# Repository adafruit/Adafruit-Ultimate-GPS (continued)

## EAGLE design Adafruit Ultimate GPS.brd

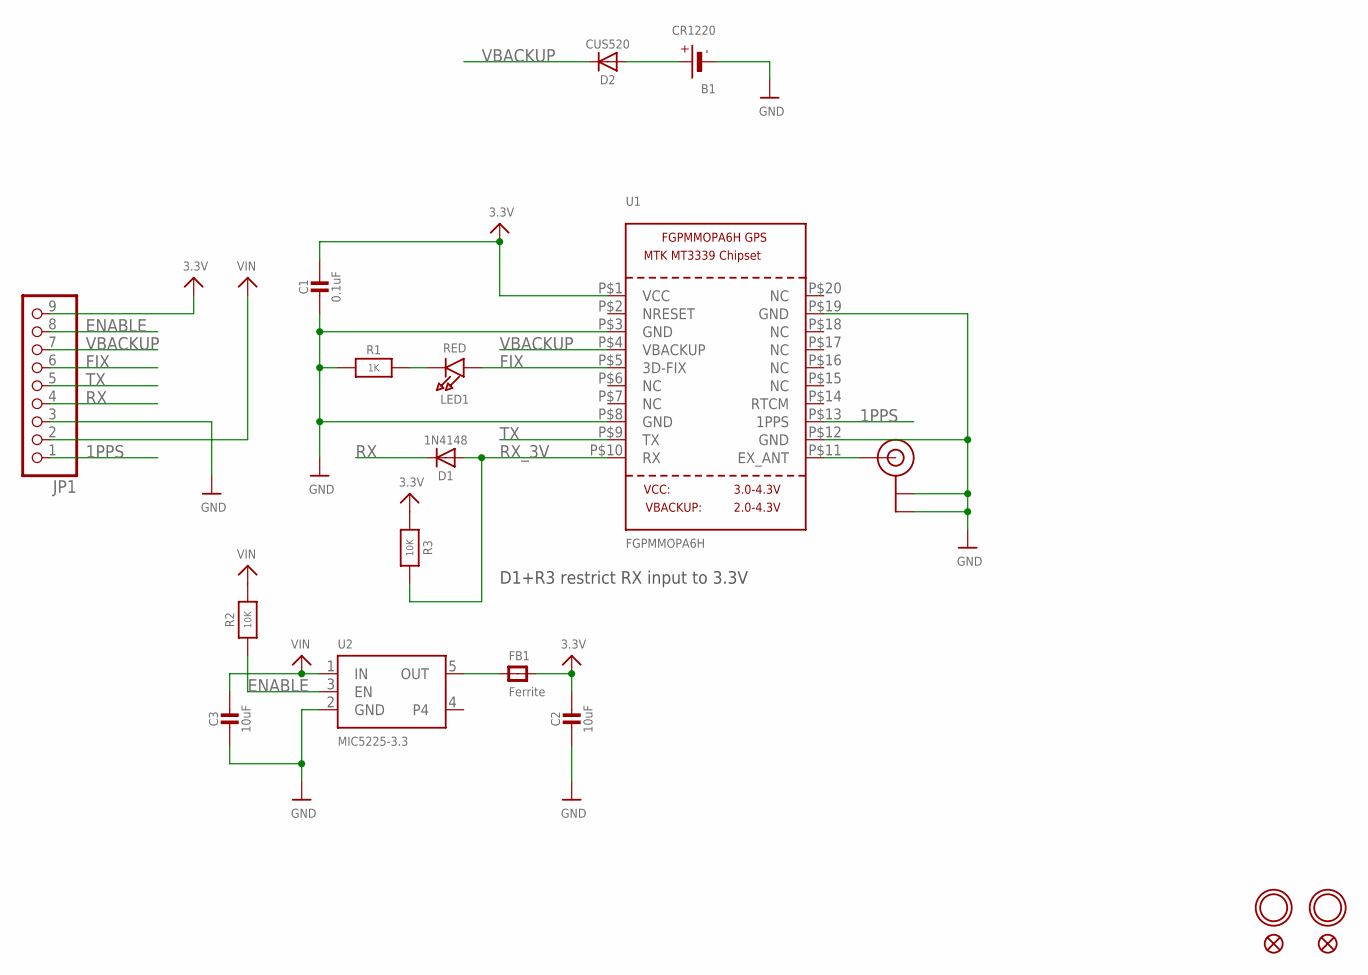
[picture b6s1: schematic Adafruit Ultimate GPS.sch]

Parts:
B1: CR1220
C1: 0.1uF; 0805-NO
C2, C3: 10uF; 0805-NO
D1: 1N4148; SOD-323
D2: CUS520; SOD-323
FB1: Ferrite; 0805-NO
FID1, FID2: FIDUCIAL""; FIDUCIAL_1MM
JP1: HEADER-1X970MIL; 1X09_ROUND_70
LED1: RED; CHIPLED_0805
R1: 1K; 0805-NO
R2, R3: 10K; 0805-NO
U1: FGPMMOPA6H
U2: MIC5225-3.3; SOT23-5
U$8, U$9: MOUNTINGHOLE2.5; MOUNTINGHOLE_2.5_PLATED
U$20: U.FL

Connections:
1PPS: JP1.1, U1.P$13 (1PPS)
3.3V: C1.1, C2.1, FB1.2, JP1.9, R3.1, U1.P$1 (VCC)
ENABLE: JP1.8, R2.1, U2.3 (EN)
FIX: JP1.6, LED1.A, U1.P$5 (3D-FIX)
GND: B1.-, C1.2, C2.2, C3.2, JP1.3, R1.1, U1.P$3 (GND), U1.P$8 (GND), U1.P$12 (GND), U1.P$19 (GND), U2.2 (GND), U$20.P$1 (GND), U$20.P$2 (GND)
unnamed: B1.+$1 (+), B1.+$2 (+), D2.A
unnamed: LED1.C, R1.2
unnamed: FB1.1, U2.5 (OUT)
unnamed: U1.P$11 (EX_ANT), U$20.P$3 (SIGNAL)
RX: D1.C, JP1.4
RX_3V: D1.A, R3.2, U1.P$10 (RX)
TX: JP1.5, U1.P$9 (TX)
VBACKUP: D2.C, JP1.7, U1.P$4 (VBACKUP)
VIN: C3.1, JP1.2, R2.2, U2.1 (IN)

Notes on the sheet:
D1+R3 restrict RX input to 3.3V

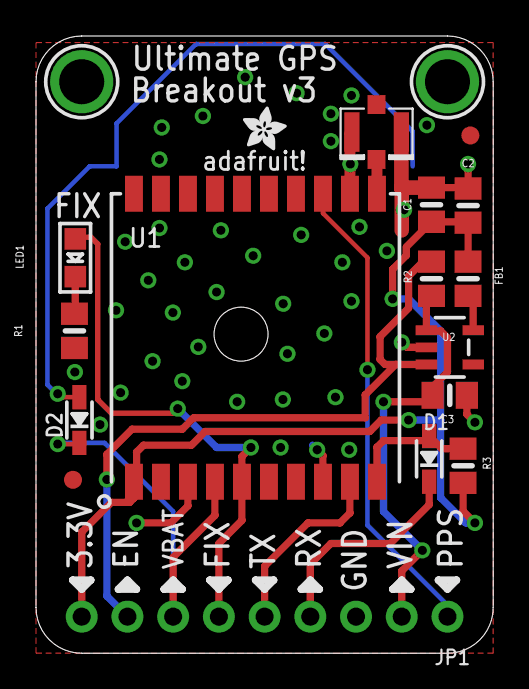
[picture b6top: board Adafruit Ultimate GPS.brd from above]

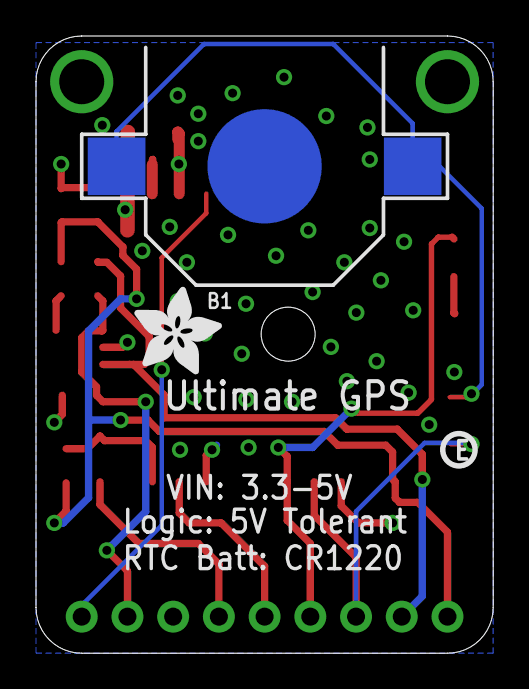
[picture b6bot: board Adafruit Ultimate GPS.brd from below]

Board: 2 copper layers, 25.4 x 34.3 mm, 22 parts (3 on the bottom side), 14 nets.

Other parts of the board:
U$15: ADAFRUIT_2.5MM
U$16: PCBFEAT-REV-040
U$18: ADAFRUIT_5MM

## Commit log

2012-04-20 Ultimate!
2014-07-25 Gerber Added, Polygon adjusted
    Created gerber files from Seeedstudio 2-layer gerber generator, Fixed
    .brd file, Edited GND polygon by ratnest command
2014-07-25 Added Copper on Top Layer
2014-07-25 Garbage Deleted
2014-07-25 Modified Value Position
2017-11-12 updated!
2019-06-12 Add Ultimate GPS USB board files
2019-11-09 Made a EagleCad Library for Adafruit Ultimate GPS breakout board
2019-11-09 Changed dimension to tplace layer
2022-03-17 Add USB-C board files.
2022-03-18 Cookiecutted and added all the ultimate GPSs
